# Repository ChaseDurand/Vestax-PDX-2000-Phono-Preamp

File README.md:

# Vestax PDX-2000 Phono Preamp
Integrated phono preamp for Vestax PDX-2000 turntables.

Specs:
* Gain ~42.7dB at 1kHz.
* Loading 47kΩ, 360pF.
* Simulated amplitude within +/-0.05dB of RIAA.
* Actual amplitude within +/-0.5dB of RIAA.
* Left/right channel amplitude within +/-0.22dB.
* Left/right channel phase within +/-0.67°.

This amplifier is designed for moving magnet catridges- specifically around the Shure M44-7 and Ortofon Mix Concorde Mk II.

The board uses existing PCB screws on board P100 to mount in the chasis. The existing cable on J704 is re-routed to J4, and new wires and an 11-pin JST connector go to J704. The tonearm wires are routed to the input section of the PCB, and new wires connect the output of the amplifier to the original output PCB and RCA jacks. Board taps into internal +15V/-15V/GND for power (with 12V regulators for ripple reduction).

Overall performance is very good with minimal deviations from RIAA, simulation, and left/right channels. Note that some plots below use a heavily magnified delta on the right axis.

The [LTspice simulation](spice/) closely follows the RIAA amplitude curve within +/-0.05dB:

Simulations with 1% tolerance parts give a max amplitude error of +/-0.15dB:

The actual amplitude error is within +/-0.5dB, with the majority being within +/-0.1dB:

The frequency response of the left and right channels is closely matched:

The phase is very similar to the simulation:

The phase response of the left and right channels is closely matched:

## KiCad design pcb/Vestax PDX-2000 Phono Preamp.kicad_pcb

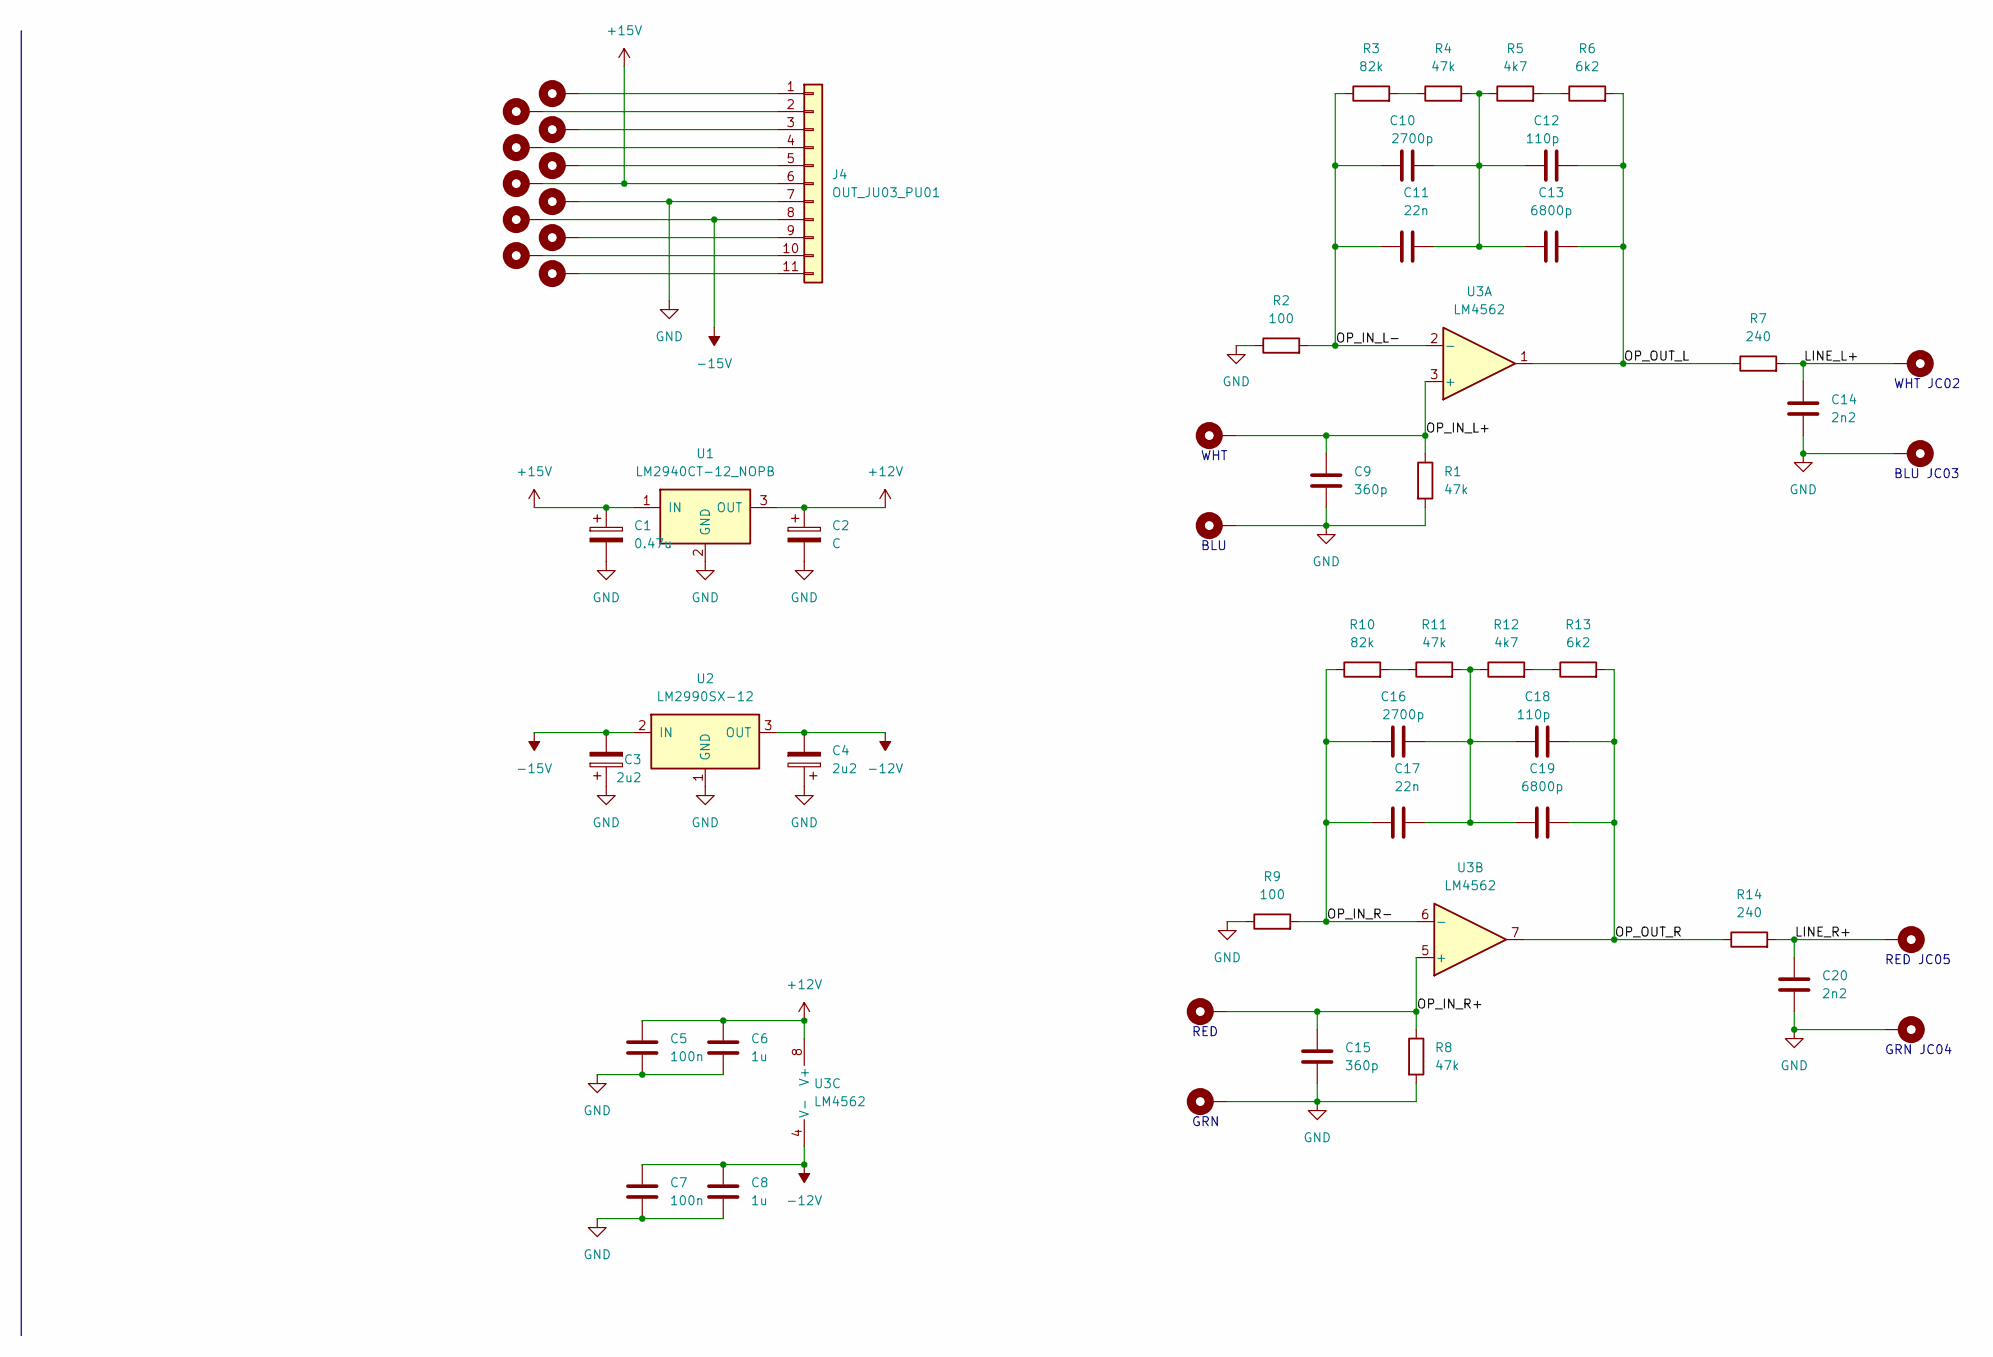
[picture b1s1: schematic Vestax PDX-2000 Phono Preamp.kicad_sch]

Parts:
C1: 0.47u; CP_Radial_Tantal_D4.5mm_P2.50mm
C2: C; CP_Radial_Tantal_D9.0mm_P5.00mm
C3, C4: 2u2; CP_Radial_Tantal_D4.5mm_P2.50mm
C5, C7: 100n; C_0805_2012Metric
C6, C8: 1u; C_0805_2012Metric
C9, C15: 360p; C_Axial_L5.1mm_D3.1mm_P7.50mm_Horizontal
C10, C16: 2700p; C_Disc_D3.8mm_W2.6mm_P2.50mm; Mfr. # C315C272F3G5TA
C11, C17: 22n; C_Rect_L7.5mm_W6.5mm_P5.00mm
C12, C18: 110p; C_Disc_D3.8mm_W2.6mm_P2.50mm; Mfr. # C320C111F3G5TA
C13, C19: 6800p; C_Disc_D3.8mm_W2.6mm_P2.50mm
C14, C20: 2n2; C_Disc_D3.8mm_W2.6mm_P2.50mm
H1, H2, H3, H4, H5, H6, H7, H8, H9, H10, H11: MountingHole_Pad; SolderWire-0.1sqmm_1x01_D0.4mm_OD1mm
H12, H13, H14, H15, H16, H17, H18, H19: MountingHole_Pad; TestPoint_Pad_D3.0mm
J4: OUT_JU03_PU01; JST_PH_B11B-PH-K_1x11_P2.00mm_Vertical
R1, R4, R8, R11: 47k; R_Axial_DIN0204_L3.6mm_D1.6mm_P5.08mm_Horizontal
R2, R9: 100; R_Axial_DIN0204_L3.6mm_D1.6mm_P5.08mm_Horizontal
R3, R10: 82k; R_Axial_DIN0204_L3.6mm_D1.6mm_P5.08mm_Horizontal
R5, R12: 4k7; R_Axial_DIN0207_L6.3mm_D2.5mm_P10.16mm_Horizontal
R6, R13: 6k2; R_Axial_DIN0204_L3.6mm_D1.6mm_P5.08mm_Horizontal
R7, R14: 240; R_Axial_DIN0207_L6.3mm_D2.5mm_P10.16mm_Horizontal
U1: LM2940CT-12_NOPB; TO-220-3_Vertical
U2: LM2990SX-12; TO-220-3_Vertical
U3: LM4562; DIP-8_W7.62mm_Socket; Mfr. # LM4562NA/NOPB

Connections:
+12V: C2.1, C5.2, C6.2, U1.3 (OUT), U3.8 (V+)
+15V: C1.1, H6.1, J4.6, U1.1 (IN)
-12V: C4.2, C7.2, C8.2, U2.3 (OUT), U3.4 (V-)
-15V: C3.2, H8.1, J4.8, U2.2 (IN)
/LINE_L+: C14.1, H18.1, R7.2
/LINE_R+: C20.1, H16.1, R14.2
/OP_IN_L+: C9.1, H14.1, R1.1, U3.3 (+)
/OP_IN_L-: C10.1, C11.1, R2.2, R3.1, U3.2 (-)
/OP_IN_R+: C15.1, H12.1, R8.1, U3.5 (+)
/OP_IN_R-: C16.1, C17.1, R9.2, R10.1, U3.6 (-)
/OP_OUT_L: C12.2, C13.2, R6.2, R7.1, U3.1
/OP_OUT_R: C18.2, C19.2, R13.2, R14.1, U3.7
GND: C1.2, C2.2, C3.1, C4.1, C5.1, C6.1, C7.1, C8.1, C9.2, C14.2, C15.2, C20.2, H7.1, H13.1, H15.1, H17.1, H19.1, J4.7, R1.2, R2.1, R8.2, R9.1, U1.2 (GND), U2.1 (GND)
unnamed: C10.2, C11.2, C12.1, C13.1, R4.2, R5.1
unnamed: C16.2, C17.2, C18.1, C19.1, R11.2, R12.1
unnamed: H1.1, J4.1
unnamed: H2.1, J4.2
unnamed: H3.1, J4.3
unnamed: H4.1, J4.4
unnamed: H5.1, J4.5
unnamed: H9.1, J4.9
unnamed: H10.1, J4.10
unnamed: H11.1, J4.11
unnamed: R3.2, R4.1
unnamed: R5.2, R6.1
unnamed: R10.2, R11.1
unnamed: R12.2, R13.1

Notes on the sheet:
WHT
BLU
GRN
WHT JC02
GRN JC04
RED JC05
RED
BLU JC03

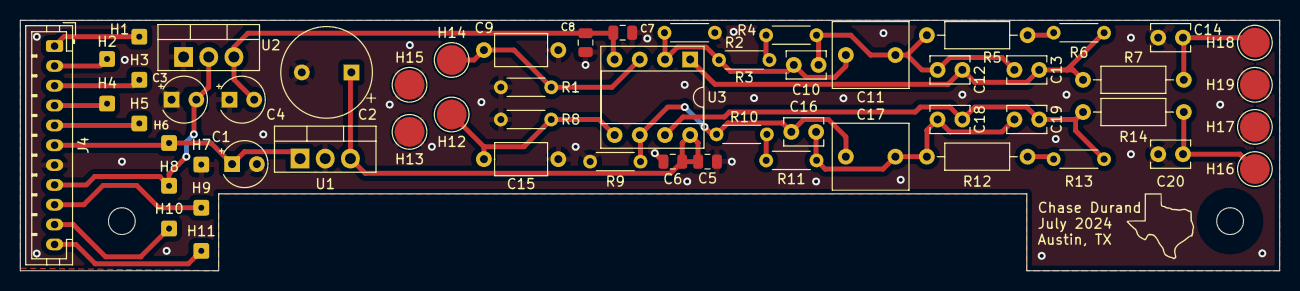
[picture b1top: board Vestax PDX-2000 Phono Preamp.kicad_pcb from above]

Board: 2 copper layers, 127.0 x 25.2 mm, 59 parts (0 on the bottom side), 27 nets.

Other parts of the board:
MH1, MH1#2: MountingHole_2.7mm_M2.5

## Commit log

2024-08-24 Added ltspice files.
2024-08-24 Added kicad pcb files.
2024-08-24 Added picture
2024-08-24 Update README.md with image
2024-08-24 Update README.md with specs
2024-08-24 Added preamp pcb image
2024-08-24 Added 3d render
2024-08-24 Update README.md with pictures
2024-08-24 Added installation image
2024-08-24 Added C2 value to schematic.
2024-08-24 Added schematic pdf.
2024-08-24 Added BOM.
2024-08-24 Added plots.
2024-08-24 Updated readme with plots. Added montecarlo plot.
2024-08-24 Corrected ltspice power supply from 15 to 12.
